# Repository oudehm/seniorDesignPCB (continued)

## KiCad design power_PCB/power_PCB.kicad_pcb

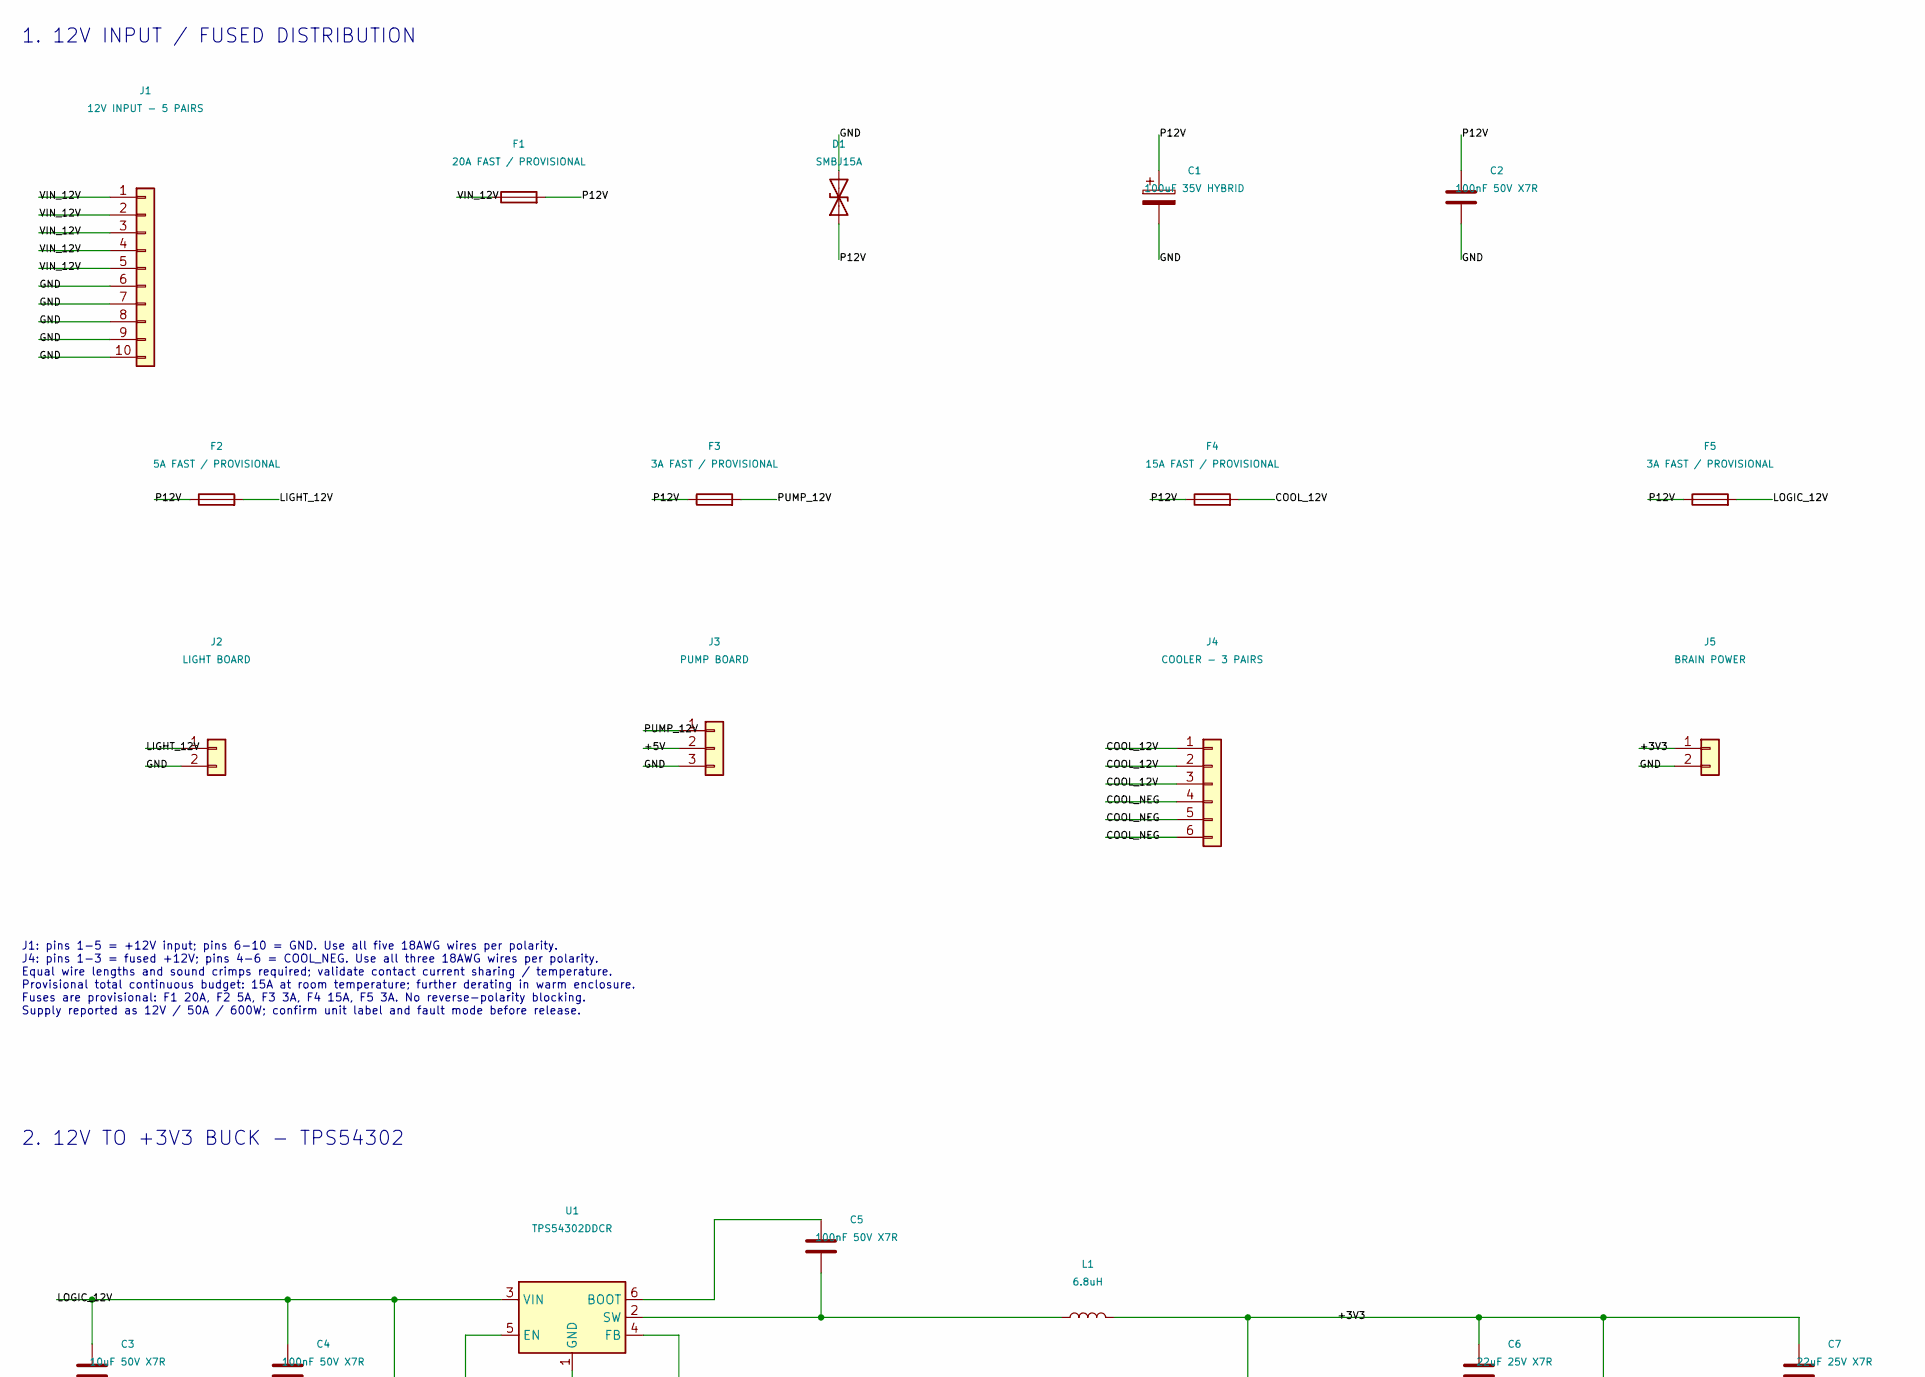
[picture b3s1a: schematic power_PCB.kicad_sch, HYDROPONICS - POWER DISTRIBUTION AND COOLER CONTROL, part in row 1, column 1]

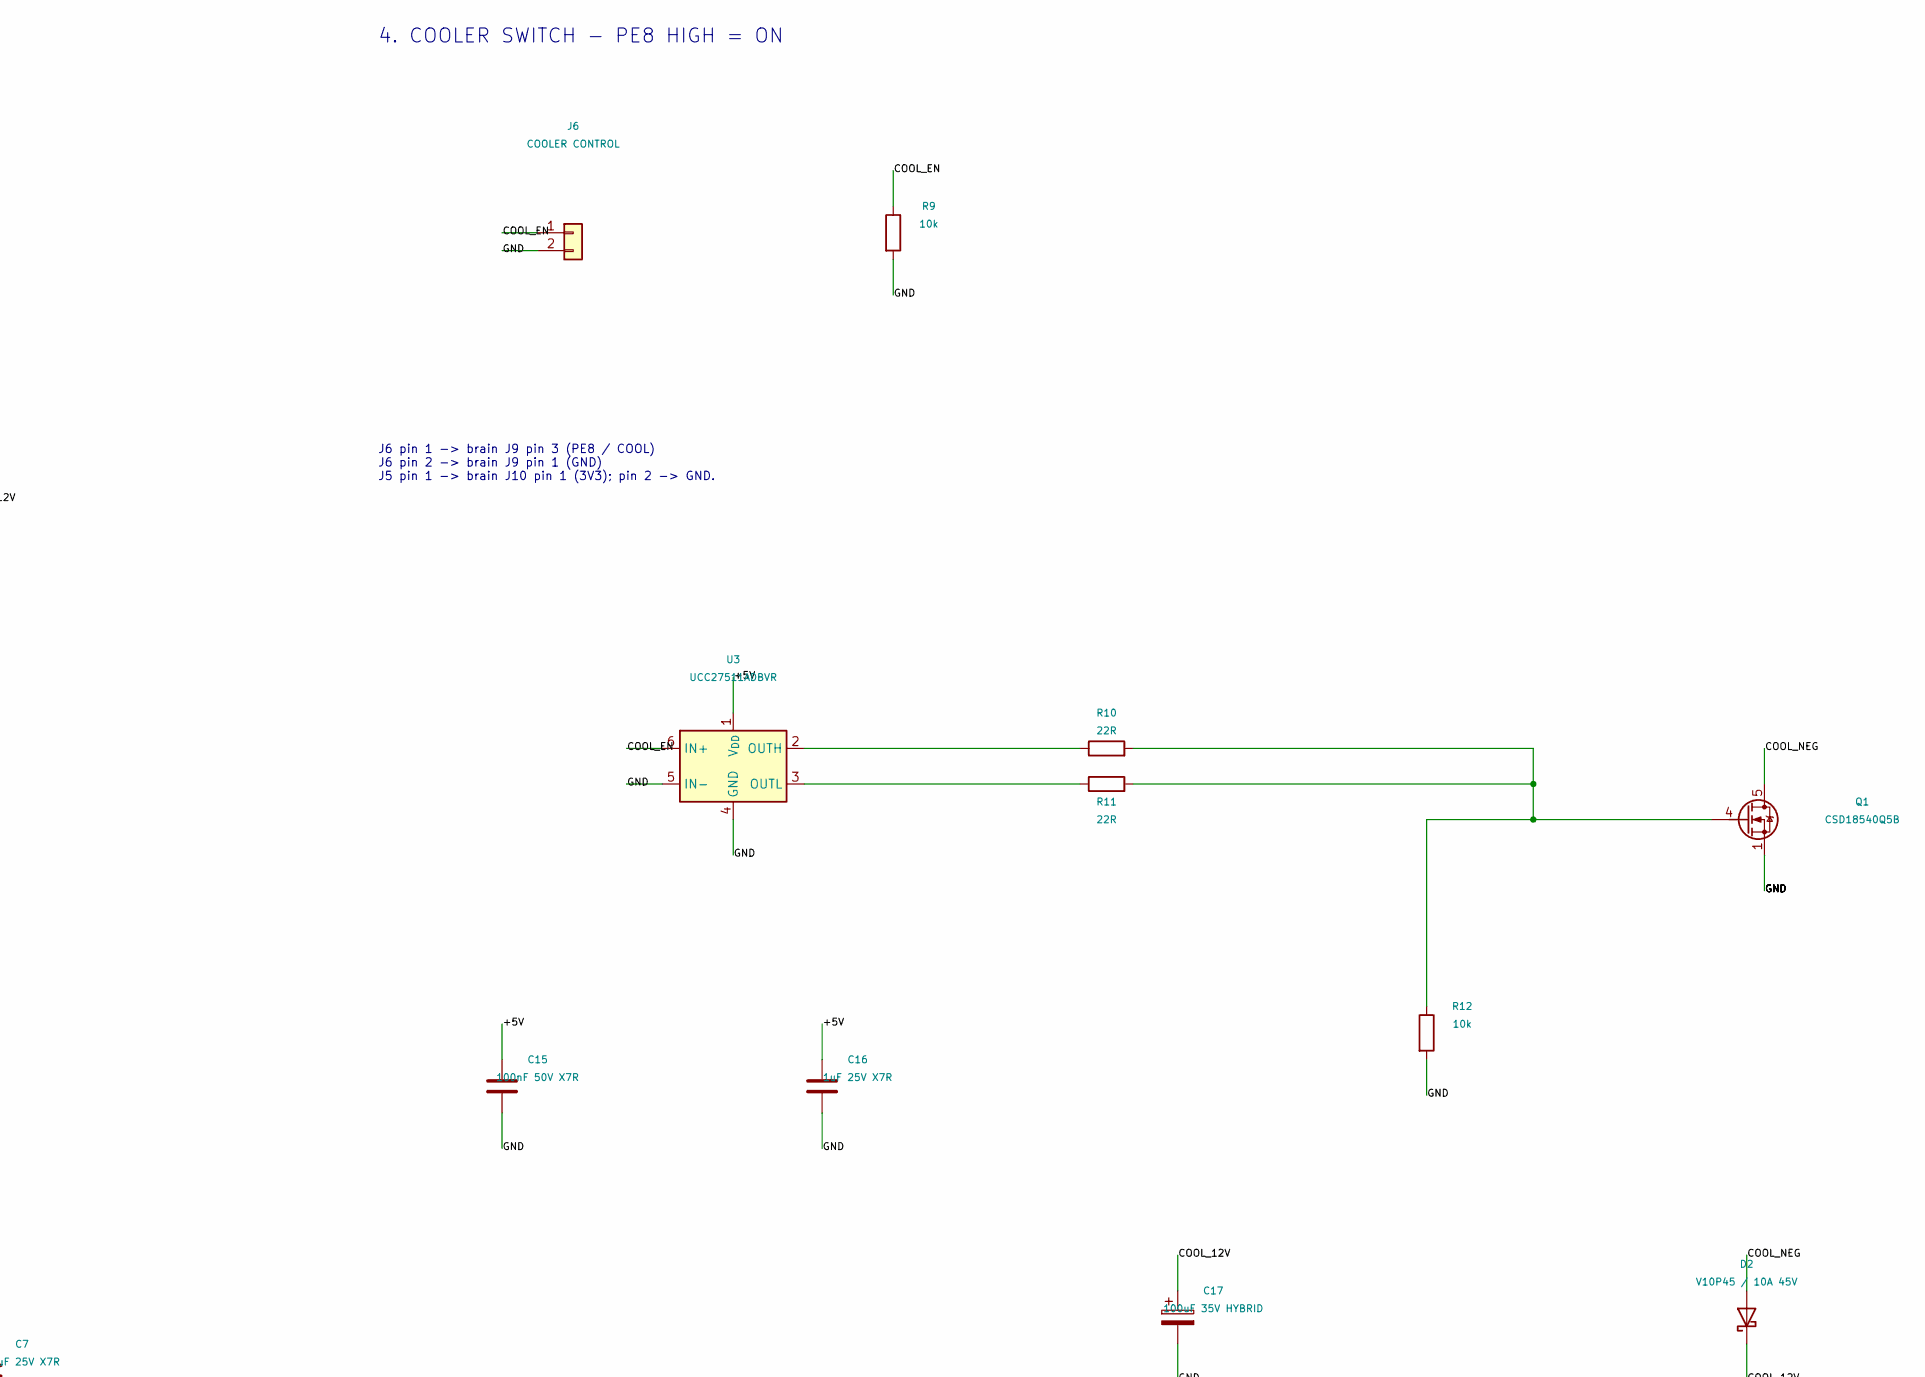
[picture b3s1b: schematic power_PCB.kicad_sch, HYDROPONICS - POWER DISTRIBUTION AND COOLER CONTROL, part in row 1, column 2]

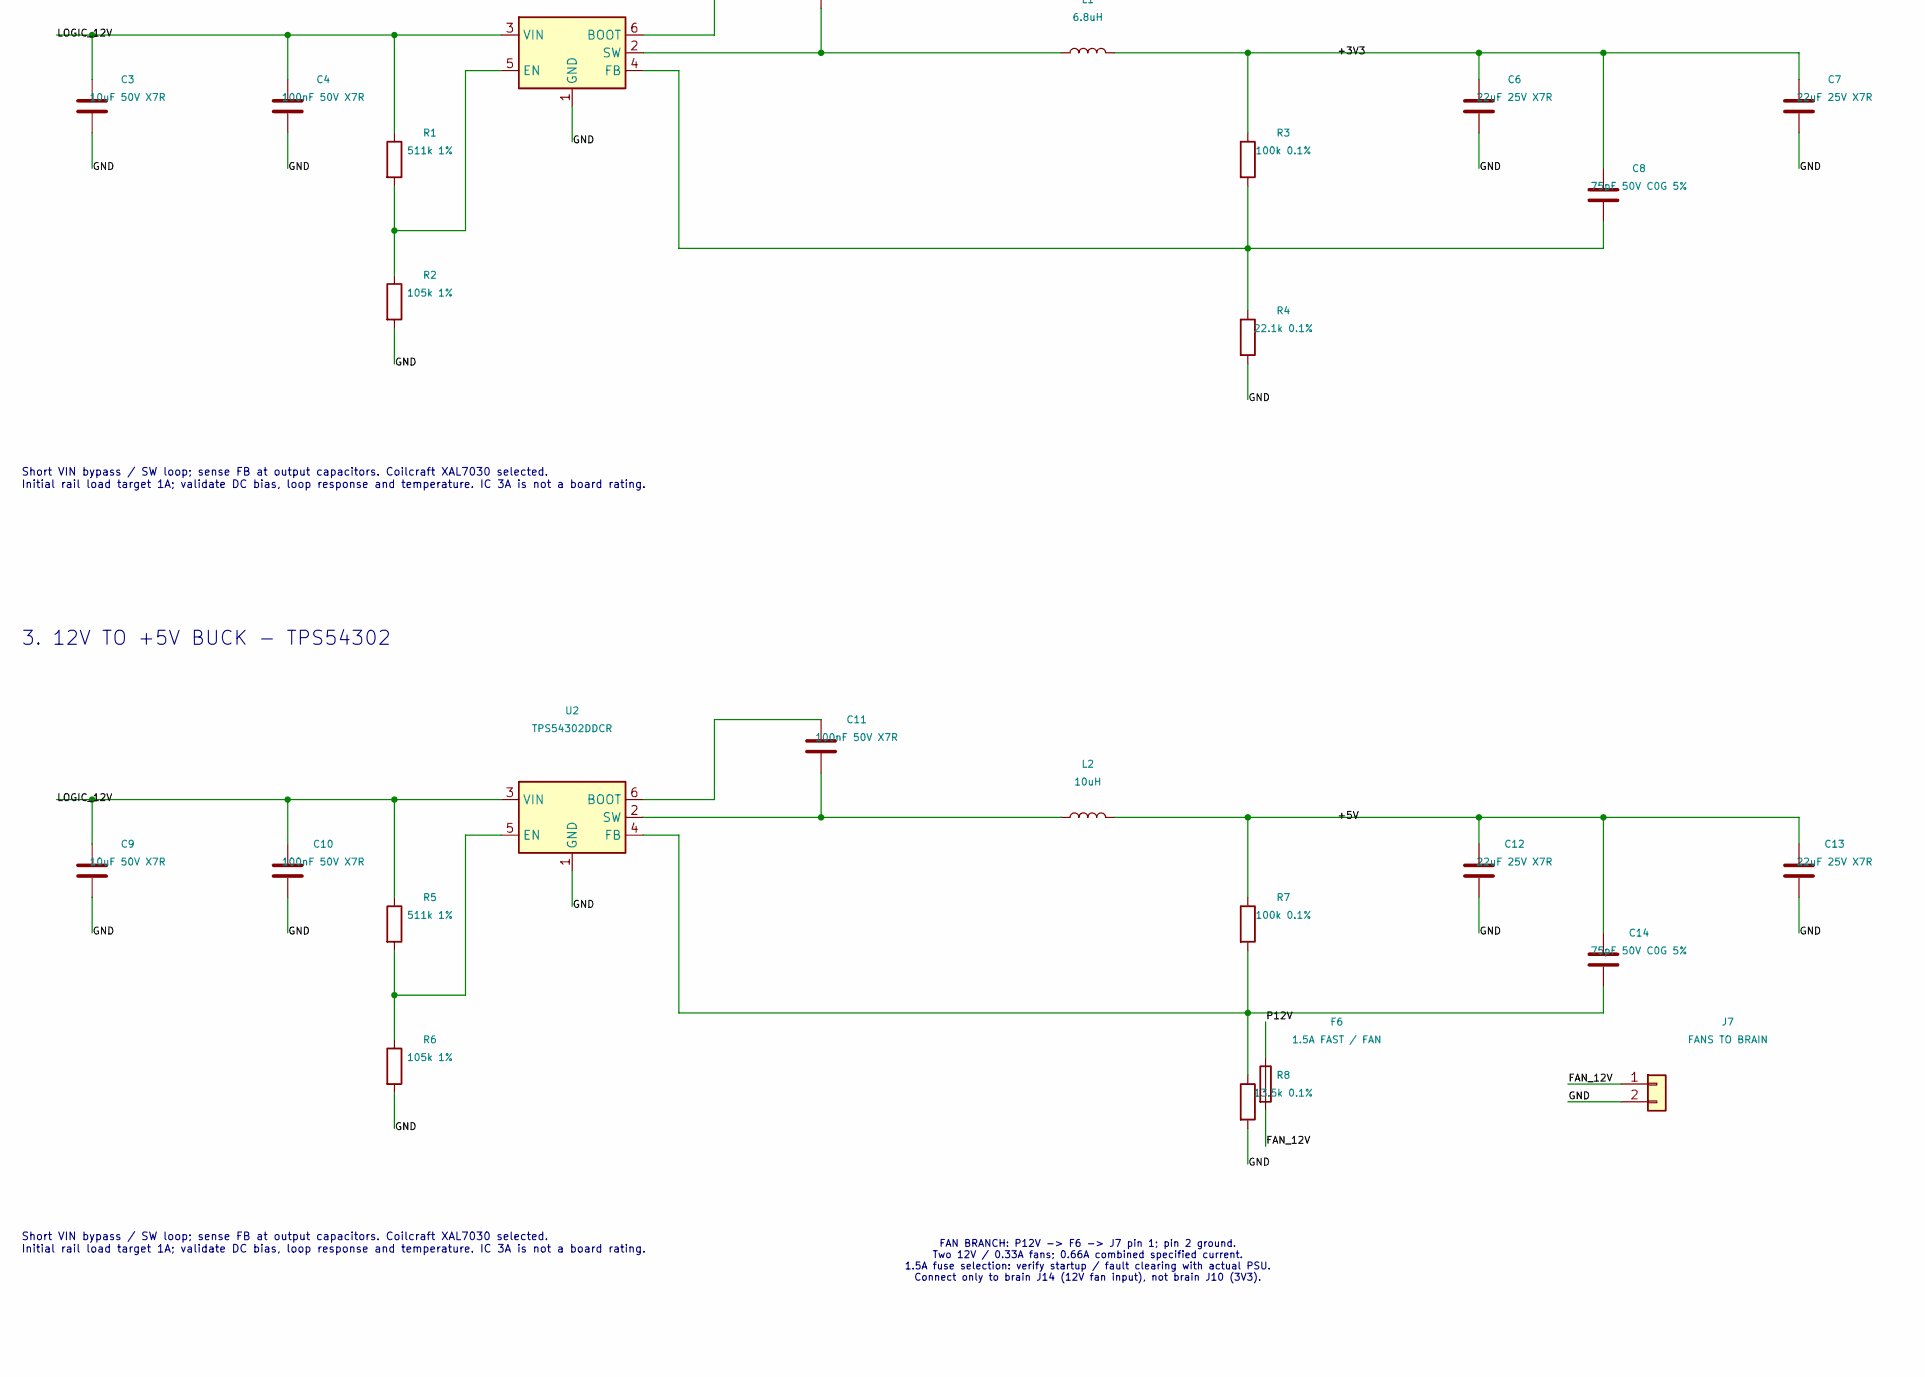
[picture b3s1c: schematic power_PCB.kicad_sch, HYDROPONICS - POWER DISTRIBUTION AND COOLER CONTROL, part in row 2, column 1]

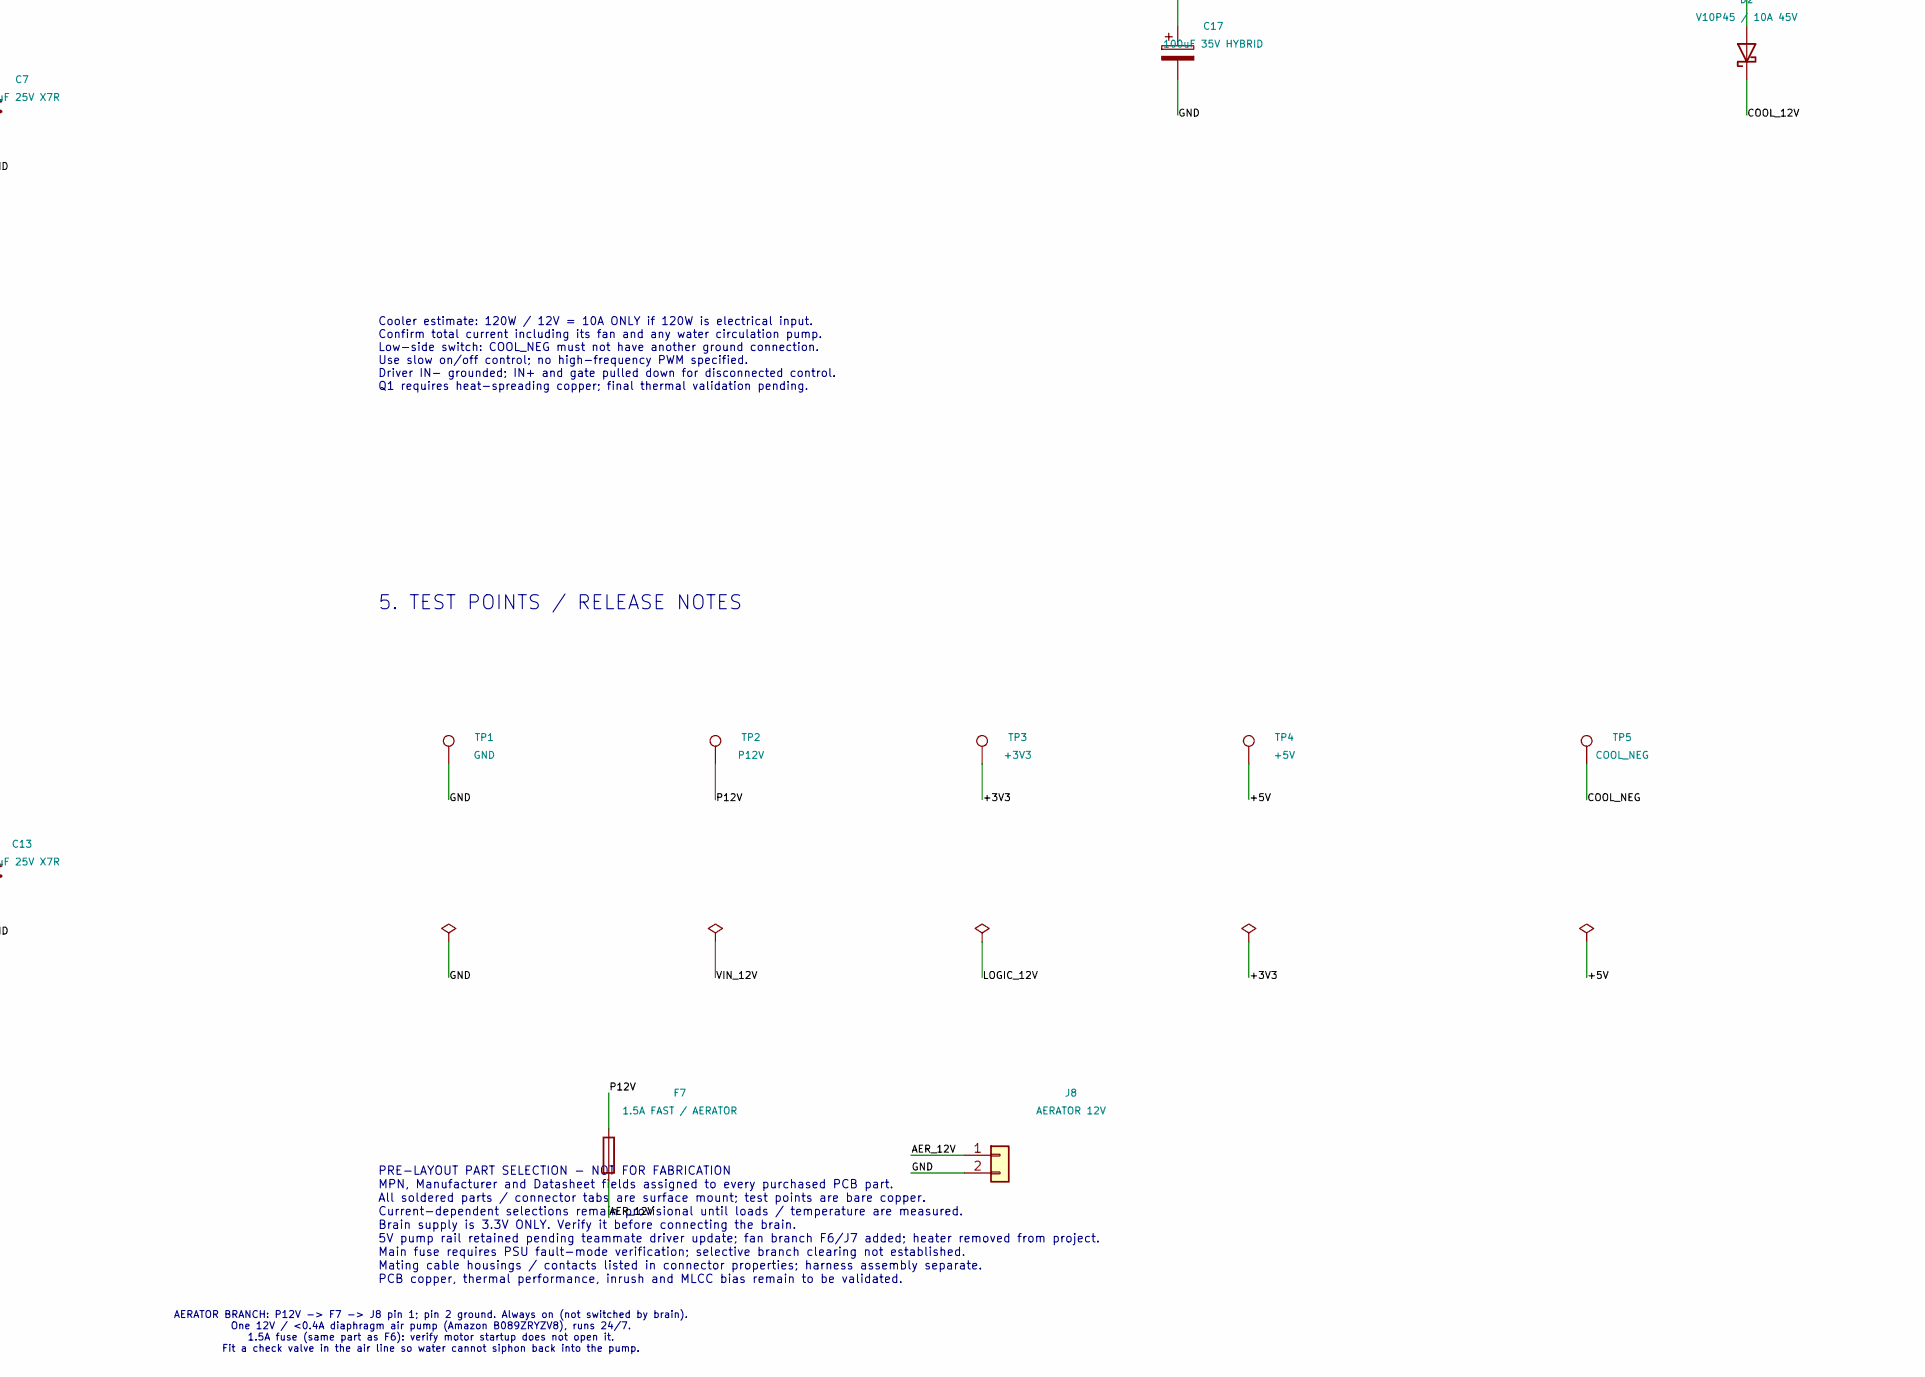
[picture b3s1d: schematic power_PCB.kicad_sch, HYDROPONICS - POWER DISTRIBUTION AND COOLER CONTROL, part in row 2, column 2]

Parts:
C1, C17: 100uF 35V HYBRID; CP_Elec_8x10.5; MPN EEHZC1V101P; LCSC C454651
C2, C4, C5, C10, C11, C15: 100nF 50V X7R; C_0805_2012Metric; MPN GRM21BR71H104KA01L; LCSC C77082
C3, C9: 10uF 50V X7R; C_1210_3225Metric; MPN GRM32ER71H106KA12L; LCSC C77102
C6, C7, C12, C13: 22uF 25V X7R; C_1210_3225Metric; MPN GRM32ER71E226KE15L; LCSC C21397
C8, C14: 75pF 50V C0G 5%; C_0805_2012Metric; MPN CC0805JRNPO9BN750; LCSC C113832
C16: 1uF 25V X7R; C_0805_2012Metric; MPN GRM21BR71E105KA99L; LCSC C77080
D1: SMBJ15A; D_SMB; MPN SMBJ15A; LCSC C83846
D2: V10P45 / 10A 45V; Vishay_V10P45_TO-277A_K1_A2; MPN V10P45HM3_A/H; LCSC C6582752
F1: 20A FAST / PROVISIONAL; Fuse_Littelfuse-NANO2-451_453; MPN 0451020.MRL; LCSC C178980
F2: 5A FAST / PROVISIONAL; Fuse_Littelfuse-NANO2-451_453; MPN 0451005.MRL; LCSC C48467
F3, F5: 3A FAST / PROVISIONAL; Fuse_Littelfuse-NANO2-451_453; MPN 0451003.MRL; LCSC C13982
F4: 15A FAST / PROVISIONAL; Fuse_Littelfuse-NANO2-451_453; MPN 0451015.MRL; LCSC C44480
F6: 1.5A FAST / FAN; Fuse_1206_3216Metric; MPN 046601.5NR; LCSC C151136
F7: 1.5A FAST / AERATOR; Fuse_1206_3216Metric; MPN 046601.5NR; LCSC C151136
J1: 12V INPUT - 5 PAIRS; Molex_Micro-Fit_3.0_43650-1015_1x10_P3.00mm_Vertical; MPN 0436501015; LCSC C17337723
J2: LIGHT BOARD; JST_XH_B2B-XH-A_1x02_P2.50mm_Vertical; MPN B2B-XH-A(LF)(SN)
J3: PUMP BOARD; JST_XH_B3B-XH-A_1x03_P2.50mm_Vertical; MPN B3B-XH-A(LF)(SN)
J4: COOLER - 3 PAIRS; Molex_Micro-Fit_3.0_43650-0615_1x06_P3.00mm_Vertical; MPN 436500615; LCSC C505231
J5: BRAIN POWER; JST_XH_B2B-XH-A_1x02_P2.50mm_Vertical; MPN B2B-XH-A(LF)(SN)
J6: COOLER CONTROL; JST_XH_B2B-XH-A_1x02_P2.50mm_Vertical; MPN B2B-XH-A(LF)(SN)
J7: FANS TO BRAIN; JST_XH_B2B-XH-A_1x02_P2.50mm_Vertical; MPN B2B-XH-A(LF)(SN)
J8: AERATOR 12V; JST_XH_B2B-XH-A_1x02_P2.50mm_Vertical; MPN B2B-XH-A(LF)(SN)
L1: 6.8uH; L_Bourns_SRP7030CA_7.6x7.8mm; MPN SRP7030CA-6R8M; LCSC C2047432
L2: 10uH; L_Coilcraft_XAL7030-103; MPN XAL7030-103MEC; LCSC C19191652
Q1: CSD18540Q5B; TDSON-8-1; MPN CSD18540Q5B; LCSC C86513
R1, R5: 511k 1%; R_0603_1608Metric; MPN RC0603FR-07511KL; LCSC C188257
R2, R6: 105k 1%; R_0603_1608Metric; Rating 105kohm 0.1%, 0603, 100mW; MPN RT0603BRD07105KL; LCSC C861072
R3, R7: 100k 0.1%; R_0603_1608Metric; MPN RT0603BRD07100KL; LCSC C122538
R4: 22.1k 0.1%; R_0603_1608Metric; MPN RT0603BRD0722K1L; LCSC C723484
R8: 13.5k 0.1%; R_0603_1608Metric; MPN RT0603BRD0713K5L; LCSC C861118
R9, R12: 10k; R_0603_1608Metric; MPN RC0603FR-0710KL; LCSC C98220
R10, R11: 22R; R_0603_1608Metric; MPN RC0603FR-0722RL; LCSC C107701
TP1: GND; TestPoint_Pad_D2.0mm_ClearSilk
TP2: P12V; TestPoint_Pad_D2.0mm_ClearSilk
TP3: +3V3; TestPoint_Pad_D2.0mm_ClearSilk
TP4: +5V; TestPoint_Pad_D2.0mm_ClearSilk
TP5: COOL_NEG; TestPoint_Pad_D2.0mm_ClearSilk
U1, U2: TPS54302DDCR; SOT-23-6; MPN TPS54302DDCR; LCSC C311983
U3: UCC27511ADBVR; SOT-23-6; MPN UCC27511ADBVR; LCSC C2676982

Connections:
/+3V3: C6.1, C7.1, C8.1, J5.1, L1.2, R3.1, TP3.1
/+5V: C12.1, C13.1, C14.1, C15.1, C16.1, J3.2, L2.2, R7.1, TP4.1, U3.1 (V_{DD})
/AER_12V: F7.2, J8.1
/COOL_12V: C17.1, D2.1 (K), F4.2, J4.1, J4.2, J4.3
/COOL_EN: J6.1, R9.1, U3.6 (IN+)
/COOL_NEG: D2.2 (A), J4.4, J4.5, J4.6, Q1.5 (D), TP5.1
/FAN_12V: F6.2, J7.1
/GND: C1.2, C2.2, C3.2, C4.2, C6.2, C7.2, C9.2, C10.2, C12.2, C13.2, C15.2, C16.2, C17.2, D1.2 (A2), J1.6, J1.7, J1.8, J1.9, J1.10, J2.2, J3.3, J5.2, J6.2, J7.2, J8.2, Q1.1 (S), Q1.2 (S), Q1.3 (S), R2.2, R4.2, R6.2, R8.2, R9.2, R12.2, TP1.1, U1.1 (GND), U2.1 (GND), U3.4 (GND), U3.5 (IN-)
/LIGHT_12V: F2.2, J2.1
/LOGIC_12V: C3.1, C4.1, C9.1, C10.1, F5.2, R1.1, R5.1, U1.3 (VIN), U2.3 (VIN)
/P12V: C1.1, C2.1, D1.1 (A1), F1.2, F2.1, F3.1, F4.1, F5.1, F6.1, F7.1, TP2.1
/PUMP_12V: F3.2, J3.1
/VIN_12V: F1.1, J1.1, J1.2, J1.3, J1.4, J1.5
unnamed: Q1.4 (G), R10.2, R11.2, R12.1
unnamed: C5.1, U1.6 (BOOT)
unnamed: R1.2, R2.1, U1.5 (EN)
unnamed: C8.2, R3.2, R4.1, U1.4 (FB)
unnamed: C5.2, L1.1, U1.2 (SW)
unnamed: C11.1, U2.6 (BOOT)
unnamed: R5.2, R6.1, U2.5 (EN)
unnamed: C14.2, R7.2, R8.1, U2.4 (FB)
unnamed: C11.2, L2.1, U2.2 (SW)
unnamed: R10.1, U3.2 (OUTH)
unnamed: R11.1, U3.3 (OUTL)

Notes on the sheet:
AERATOR BRANCH: P12V -> F7 -> J8 pin 1; pin 2 ground. Always on (not switched by brain). One 12V / <0.4A diaphragm air pump (Amazon B089ZRYZV8), runs 24/7. 1.5A fuse (same part as F6): verify motor startup does not open it. Fit a check valve in the air line so water cannot siphon back into the pump.
1. 12V INPUT / FUSED DISTRIBUTION
J1: pins 1-5 = +12V input; pins 6-10 = GND. Use all five 18AWG wires per polarity. J4: pins 1-3 = fused +12V; pins 4-6 = COOL_NEG. Use all three 18AWG wires per polarity. Equal wire lengths and sound crimps required; validate contact current sharing / temperature. Provisional total continuous budge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
2. 12V TO +3V3 BUCK - TPS54302
Short VIN bypass / SW loop; sense FB at output capacitors. Coilcraft XAL7030 selected. Initial rail load target 1A; validate DC bias, loop response and temperature. IC 3A is not a board rating.
3. 12V TO +5V BUCK - TPS54302
4. COOLER SWITCH - PE8 HIGH = ON
J6 pin 1 -> brain J9 pin 3 (PE8 / COOL) J6 pin 2 -> brain J9 pin 1 (GND) J5 pin 1 -> brain J10 pin 1 (3V3); pin 2 -> GND.
Cooler estimate: 120W / 12V = 10A ONLY if 120W is electrical input. Confirm total current including its fan and any water circulation pump. Low-side switch: COOL_NEG must not have another ground connection. Use slow on/off control; no high-frequency PWM specified. Driver IN- grounded; IN+ and gate 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
5. TEST POINTS / RELEASE NOTES
PRE-LAYOUT PART SELECTION - NOT FOR FABRICATION MPN, Manufacturer and Datasheet fields assigned to every purchased PCB part. All soldered parts / connector tabs are surface mount; test points are bare copper. Current-dependent selections remain provisional until loads / temperature are measured. Br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
FAN BRANCH: P12V -> F6 -> J7 pin 1; pin 2 ground. Two 12V / 0.33A fans; 0.66A combined specified current. 1.5A fuse selection: verify startup / fault clearing with actual PSU. Connect only to brain J14 (12V fan input), not brain J10 (3V3).

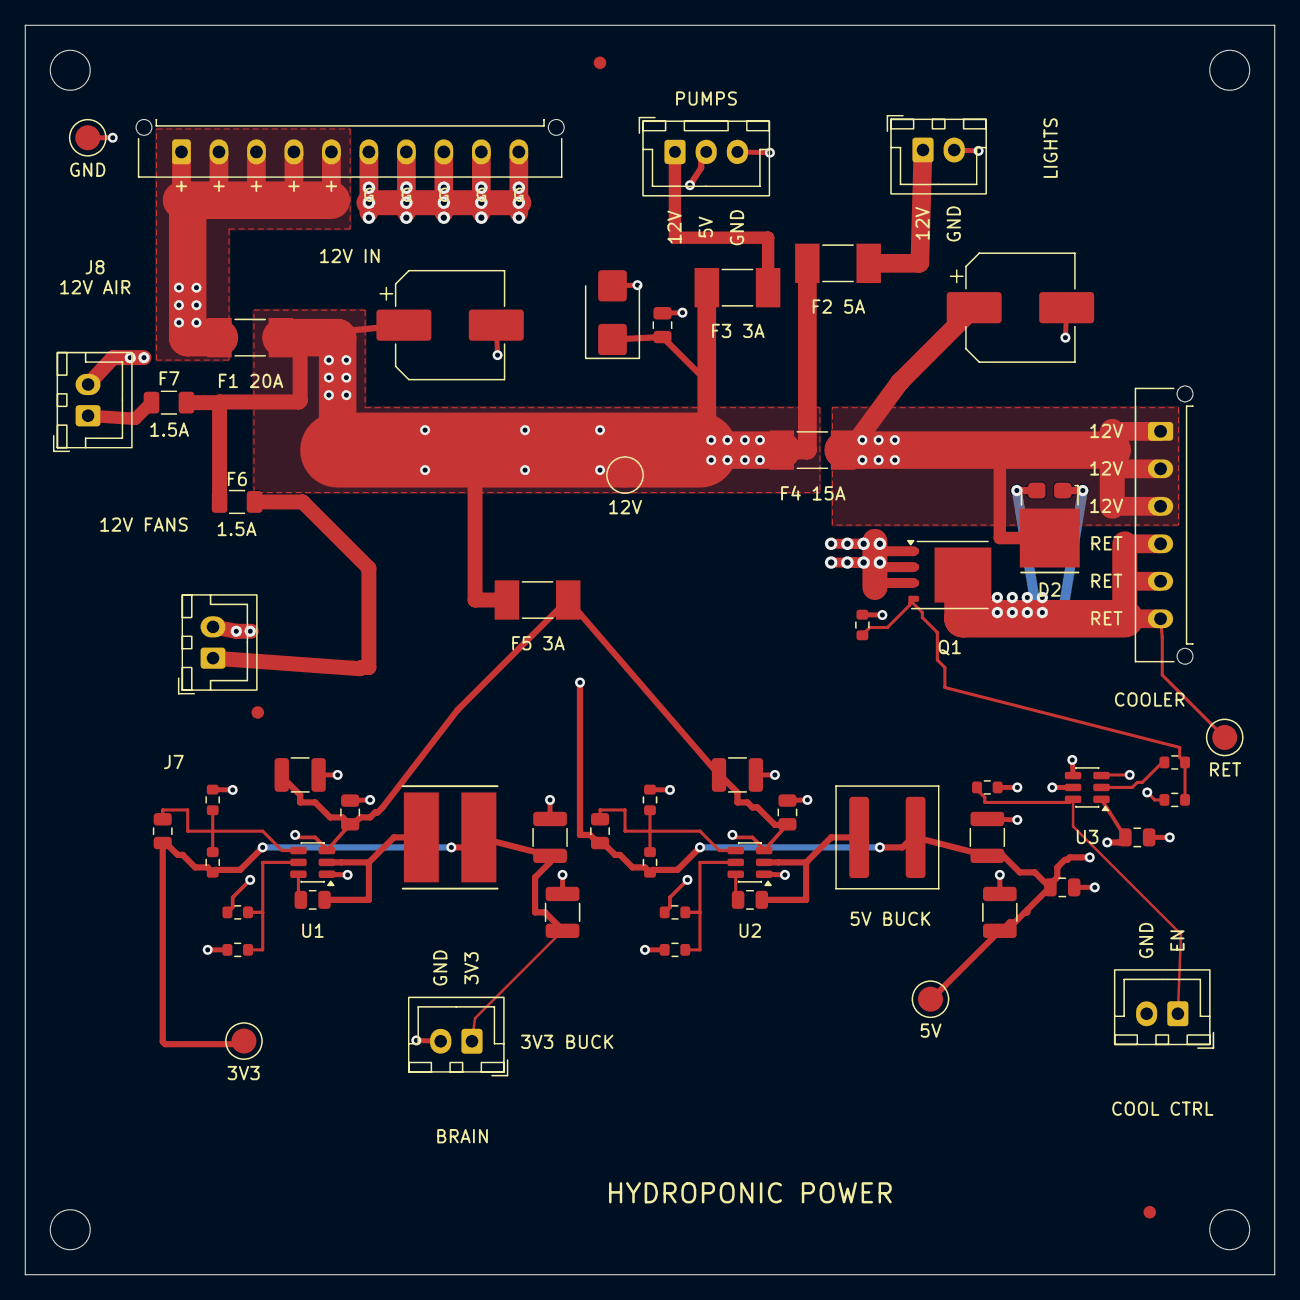
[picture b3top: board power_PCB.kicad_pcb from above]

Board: 4 copper layers, 100.0 x 100.0 mm, 64 parts (0 on the bottom side), 24 nets.

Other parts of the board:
FID1, FID2, FID3: Fiducial_1mm_Mask2mm
H1, H2, H3, H4: MountingHole_3.2mm_M3

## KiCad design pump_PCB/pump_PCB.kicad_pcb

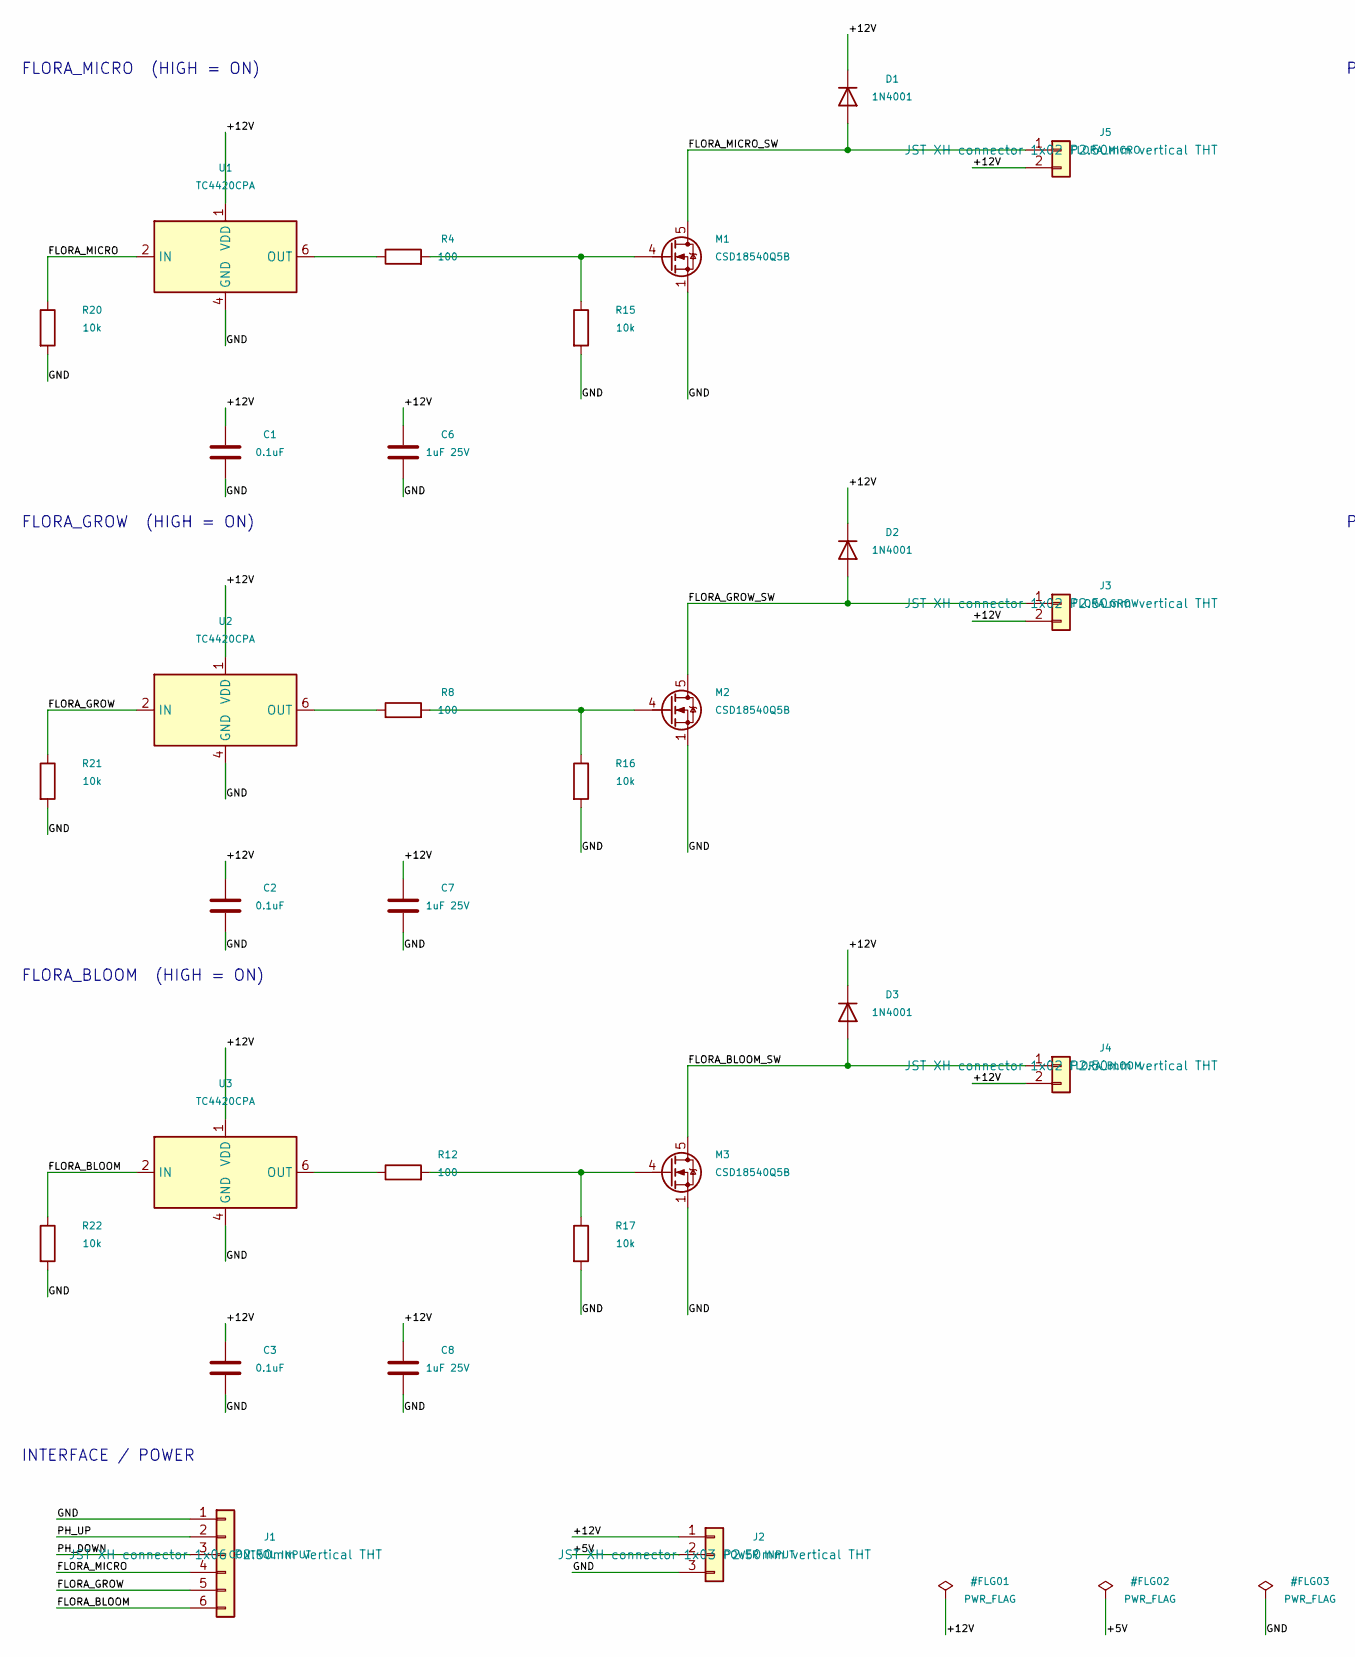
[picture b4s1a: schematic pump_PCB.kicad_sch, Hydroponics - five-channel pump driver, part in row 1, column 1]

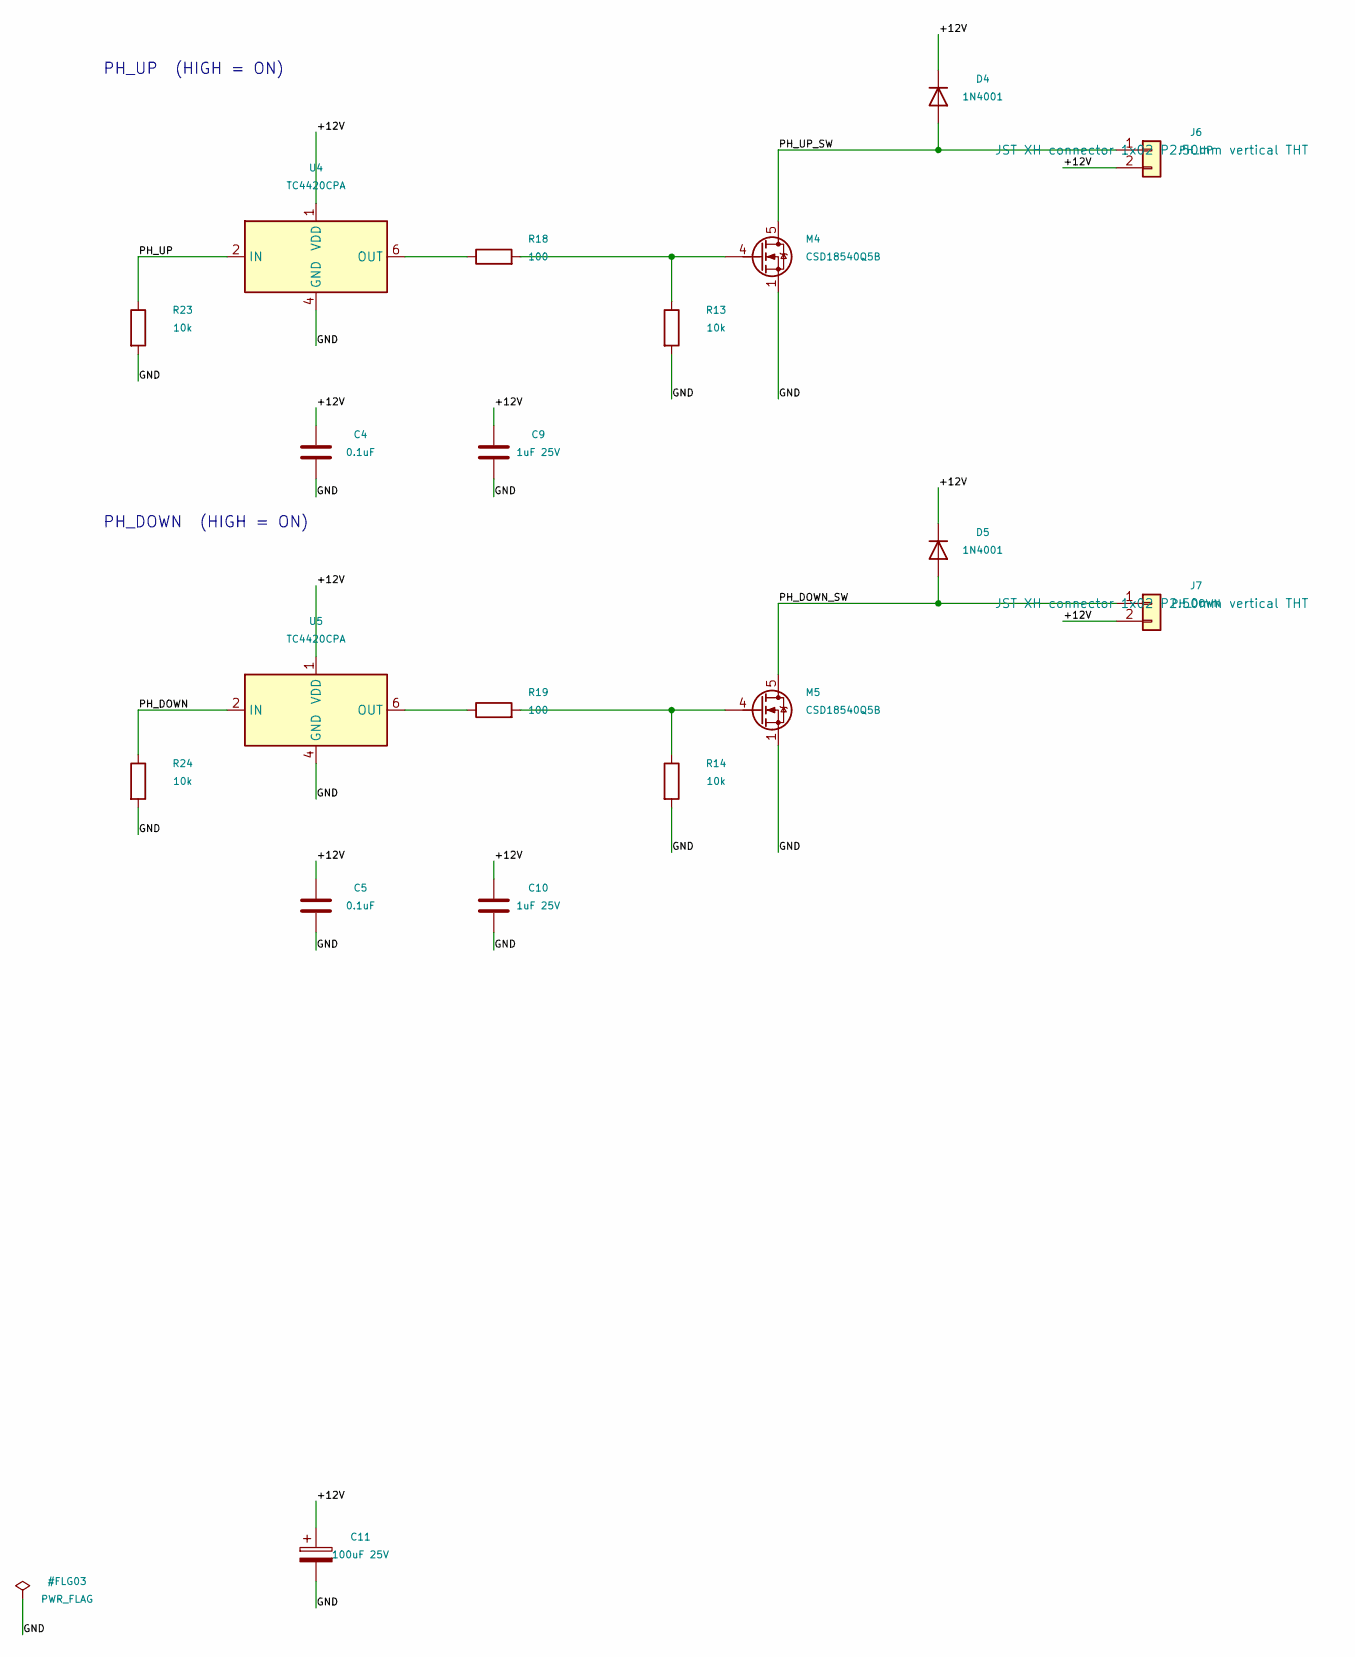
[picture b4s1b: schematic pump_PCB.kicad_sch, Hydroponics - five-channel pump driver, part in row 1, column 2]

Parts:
C1, C2, C3, C4, C5: 0.1uF; C_0603_1608Metric; Rating 100nF 50V X7R; MPN GRM188R71H104KA93D; LCSC C77055
C6, C7, C8, C9, C10: 1uF 25V; C_0603_1608Metric; Rating 1uF 25V X7R; MPN GRM188R71E105KA12D; LCSC C86020
C11: 100uF 25V; CP_Radial_D6.3mm_P2.50mm; Rating 100uF 25V, 6.3mm diameter x 11.2mm heig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; MPN EEUFM1E101; LCSC C713389
D1, D2, D3, D4, D5: 1N4001; D_DO-41_SOD81_P10.16mm_Horizontal; Rating 1A, 50V, DO-41; MPN 1N4001-E3/54; LCSC C145305
J1: CONTROL INPUT; JST_XH_B6B-XH-A_1x06_P2.50mm_Vertical; MPN B6B-XH-A(LF)(SN)
J2: POWER INPUT; JST_XH_B3B-XH-A_1x03_P2.50mm_Vertical; MPN B3B-XH-A(LF)(SN)
J3: FLORA_GROW; JST_XH_B2B-XH-A_1x02_P2.50mm_Vertical; MPN B2B-XH-A(LF)(SN)
J4: FLORA_BLOOM; JST_XH_B2B-XH-A_1x02_P2.50mm_Vertical; MPN B2B-XH-A(LF)(SN)
J5: FLORA_MICRO; JST_XH_B2B-XH-A_1x02_P2.50mm_Vertical; MPN B2B-XH-A(LF)(SN)
J6: PH_UP; JST_XH_B2B-XH-A_1x02_P2.50mm_Vertical; MPN B2B-XH-A(LF)(SN)
J7: PH_DOWN; JST_XH_B2B-XH-A_1x02_P2.50mm_Vertical; MPN B2B-XH-A(LF)(SN)
M1, M2, M3, M4, M5: CSD18540Q5B; CSD18540Q5B_TI; MPN CSD18540Q5B; LCSC C86513
R4, R8, R12, R18, R19: 100; R_Axial_DIN0207_L6.3mm_D2.5mm_P10.16mm_Horizontal; Rating 1%, 0.25W axial; formed 10.16mm lead pi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; MPN MFR-25FBF52-100R; LCSC C6300650
R13, R14, R15, R16, R17, R20, R21, R22, R23, R24: 10k; R_Axial_DIN0207_L6.3mm_D2.5mm_P10.16mm_Horizontal; Rating 1%, 0.25W axial; formed 10.16mm lead pi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; MPN MFR-25FBF52-10K; LCSC C1519255
U1, U2, U3, U4, U5: TC4420CPA; DIP-8_W7.62mm; Rating Non-inverting driver, PDIP8; 12V gate r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; MPN TC4420CPA; LCSC C48733

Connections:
/+5V: J2.2
/+12V: C1.1, C2.1, C3.1, C4.1, C5.1, C6.1, C7.1, C8.1, C9.1, C10.1, C11.1, D1.1 (K), D2.1 (K), D3.1 (K), D4.1 (K), D5.1 (K), J2.1, J3.2, J4.2, J5.2, J6.2, J7.2, U1.1 (VDD), U1.8 (VDD), U2.1 (VDD), U2.8 (VDD), U3.1 (VDD), U3.8 (VDD), U4.1 (VDD), U4.8 (VDD), U5.1 (VDD), U5.8 (VDD)
/FLORA_BLOOM: J1.6, R22.1, U3.2 (IN)
/FLORA_BLOOM_SW: D3.2 (A), J4.1, M3.5 (D)
/FLORA_GROW: J1.5, R21.1, U2.2 (IN)
/FLORA_GROW_SW: D2.2 (A), J3.1, M2.5 (D)
/FLORA_MICRO: J1.4, R20.1, U1.2 (IN)
/FLORA_MICRO_SW: D1.2 (A), J5.1, M1.5 (D)
/GND: C1.2, C2.2, C3.2, C4.2, C5.2, C6.2, C7.2, C8.2, C9.2, C10.2, C11.2, J1.1, J2.3, M1.1 (S), M1.2 (S), M1.3 (S), M2.1 (S), M2.2 (S), M2.3 (S), M3.1 (S), M3.2 (S), M3.3 (S), M4.1 (S), M4.2 (S), M4.3 (S), M5.1 (S), M5.2 (S), M5.3 (S), R13.2, R14.2, R15.2, R16.2, R17.2, R20.2, R21.2, R22.2, R23.2, R24.2, U1.4 (GND), U1.5 (GND), U2.4 (GND), U2.5 (GND), U3.4 (GND), U3.5 (GND), U4.4 (GND), U4.5 (GND), U5.4 (GND), U5.5 (GND)
/PH_DOWN: J1.3, R24.1, U5.2 (IN)
/PH_DOWN_SW: D5.2 (A), J7.1, M5.5 (D)
/PH_UP: J1.2, R23.1, U4.2 (IN)
/PH_UP_SW: D4.2 (A), J6.1, M4.5 (D)
unnamed: M1.4 (G), R4.2, R15.1
unnamed: M2.4 (G), R8.2, R16.1
unnamed: M3.4 (G), R12.2, R17.1
unnamed: M4.4 (G), R13.1, R18.2
unnamed: M5.4 (G), R14.1, R19.2
unnamed: R4.1, U1.6 (OUT), U1.7 (OUT)
unnamed: R8.1, U2.6 (OUT), U2.7 (OUT)
unnamed: R12.1, U3.6 (OUT), U3.7 (OUT)
unnamed: R18.1, U4.6 (OUT), U4.7 (OUT)
unnamed: R19.1, U5.6 (OUT), U5.7 (OUT)

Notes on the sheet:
FLORA_BLOOM (HIGH = ON)
PH_UP (HIGH = ON)
FLORA_MICRO (HIGH = ON)
PH_DOWN (HIGH = ON)
INTERFACE / POWER
FLORA_GROW (HIGH = ON)
